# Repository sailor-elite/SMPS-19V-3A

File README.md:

# SMPS SPECIFICATIONS
- Input Voltage: 230V AC (rectified to ~325V DC)
- Output Voltage: 19V DC
- Output Current: 3A
- Output Power: Up to 60W (maximum)

# SCHEMATIC DIAGRAM

# PCB 3D VIEW

# CALCULATION

### Transformer Turns Ratio Calculation

To determine the turns ratio of a transformer, use the following formula:

Np / Ns = Vin / (Vout + Vd)

Where:  
- **\(N_p\)**: Number of primary winding turns  
- **\(N_s\)**: Number of secondary winding turns  
- **\(V_in\)**: Input voltage to the transformer (325V DC in this example)  
- **\(V_out\)**: Desired output voltage (19V DC in this case)  
- **\(V_d\)**: Voltage drop across the secondary diode (approximately 0.5V for a Schottky diode)  

#### Example Calculation:

For an output voltage of 19V:

Np / Ns = 325V / (19V + 0.5V)

Np / Ns = 325 / 19.5 ≈ 16.66

Thus, the primary-to-secondary turns ratio is approximately **17:1**.

### Turns Ratio Calculation

The number of primary turns (**Np**) can be calculated using the volt-second balance equation:

Np = (Vin × ton) / (Bmax × Ae)

Where:  
- **Vin**: Input voltage (325V)  
- **ton**: On-time of the switch (calculated based on the duty cycle, typically 50% at maximum load)  
- **Bmax**: Maximum magnetic flux density (e.g., 2000 Gauss or 0.2T for ferrite cores)  
- **Ae**: Effective cross-sectional area of the core  

#### Example Calculation:

For a switching frequency of **130 kHz** (period = 7.7µs) and a 50% duty cycle, the on-time (\(ton\)) is:

ton = 50% of 7.7µs = 3.35µs

Assume the following parameters for an ETD39 core:  
- **Bmax = 0.2T**  
- **Ae = 125mm² (125 × 10⁻⁶ m²)**  

Substitute the values into the formula:

Np = (325V × 3.35µs) / (0.2T × 125 × 10⁻⁶ m²) Np ≈ 43.5 turns

Thus, the primary winding requires approximately **44 turns**.

### Number of Secondary Turns Calculation

Using the turns ratio and the calculated number of primary turns, the number of secondary turns (**Ns**) can be calculated as follows:

Ns = Np / Turns Ratio

Where:  
- **Np**: Number of primary turns (calculated previously as 85 turns)  
- **Turns Ratio**: Primary-to-secondary turns ratio (17:1 in this example)  

#### Example Calculation:

Substitute the values into the formula:

Ns = 44 / 17 Ns ≈ 2.5 turns

So the turns number is **3**.
### Reference Voltage

Using a voltage divider with resistors of **150 kΩ** and **10.2 kΩ** creates the following ratio:

Vout = Vin * (R_lower / (R_upper + R_lower))

Where:  
- **Vin**: Input voltage  
- **R_lower**: Resistor connected to the ground (10.2 kΩ)  
- **R_upper**: Resistor connected to the input voltage (150 kΩ)  

#### Example Calculation:

For an input voltage of **19V**:

Vout = 19V * (10.2 kΩ / (150 kΩ + 10.2 kΩ))

Vout = 19V * (10.2 / 160.2) ≈ 1.21V

This is very close to the reference voltage of the **MAX6101**, which is **1.25V**.

# COMPONENTS
| Component        | Value          | Package                                    | Quantity |
|------------------|----------------|--------------------------------------------|----------|
| C1               | 0.01uF/275VAC  | Capacitor_THT:C_Rect_L10.0mm_W4.0mm_P7.50mm_MKS4 | 1        |
| C2, C3           | 68uF/450V      | Capacitor_THT:CP_Radial_D12.5mm_P7.50mm    | 2        |
| C4               | 470pF/630V     | Capacitor_SMD:C_1206_3216Metric            | 1        |
| C5               | 22uF/50V       | Capacitor_THT:CP_Radial_D4.0mm_P2.00mm     | 1        |
| C6, C9, C10, C15 | 0.1uF/50V      | -- mixed values --                         | 4        |
| C7               | 4.7uF/50V      | Capacitor_SMD:C_1206_3216Metric            | 1        |
| C8               | 10000pF/100V   | Capacitor_SMD:C_1206_3216Metric            | 1        |
| C11              | 16pF/100V      | Capacitor_SMD:C_1206_3216Metric            | 1        |
| C12              | 10uF/50V       | Capacitor_THT:CP_Radial_D12.5mm_P7.50mm    | 1        |
| C13, C14         | 50uF/120V      | Capacitor_THT:CP_Radial_D12.5mm_P7.50mm    | 2        |
| C16              | 2200pF/100V    | Capacitor_THT:C_Disc_D4.3mm_W1.9mm_P5.00mm | 1        |
| D1               | DF06M          | Diode_THT:Diode_Bridge_DIP-4_W7.62mm_P5.08mm | 1        |
| D2               | 1N4148W        | Diode_SMD:D_SOD-123                        | 1        |
| D3               | UF5406         | Diode_THT:D_DO-201AD_P15.24mm_Horizontal   | 1        |
| D4               | ESD5Zxx        | Diode_SMD:D_SOD-523                        | 1        |
| D5, D6           | SS310          | Diode_SMD:D_SMA                            | 2        |
| F1               | 1000mA         | Fuse:Fuse_Littelfuse-NANO2-462             | 1        |
| J1               | 6160.0159      | private:61600159                           | 1        |
| L1               | L_Coupled_1342 | private:WE-SL5_HC                          | 1        |
| Q1               | BSP135H6433XTMA1| private:SOT230P700X180-4N                  | 1        |
| Q2               | C3M0065090D    | Package_TO_SOT_THT:TO-247-3_Vertical       | 1        |
| R1, R2           | 499K           | Resistor_SMD:R_1206_3216Metric             | 2        |
| R3, R4           | 20K            | Resistor_SMD:R_0805_2012Metric             | 2        |
| R5               | 100            | Resistor_SMD:R_0805_2012Metric             | 1        |
| R6               | 2M             | Resistor_SMD:R_0805_2012Metric             | 1        |
| R7               | 10K            | Resistor_SMD:R_0805_2012Metric             | 1        |
| R8               | 499            | Resistor_SMD:R_0805_2012Metric             | 1        |
| R9               | 14.7K          | Resistor_SMD:R_0805_2012Metric             | 1        |
| R10              | 4.42k          | Resistor_SMD:R_0805_2012Metric             | 1        |
| R11              | 4.75           | Resistor_SMD:R_0805_2012Metric             | 1        |
| R12              | 0.15           | Resistor_THT:R_Axial_DIN0922_L20.0mm_D9.0mm_P25.40mm_Horizontal | 1 |
| R13              | 150k           | Resistor_SMD:R_0805_2012Metric             | 1        |
| R14              | 10.2k          | Resistor_SMD:R_0805_2012Metric             | 1        |
| R15              | 10k            | Resistor_SMD:R_0805_2012Metric             | 1        |
| RV1              | 10D561K        | Varistor:RV_Disc_D7mm_W3.6mm_P5mm          | 1        |
| U1               | LM5023         | Package_SO:VSSOP-8_3.0x3.0mm_P0.65mm       | 1        |
| U2               | PC817          | Package_DIP:DIP-4_W7.62mm                  | 1        |
| U3               | 750313417      | private:SMD_13417_WRE                      | 1        |
| U5               | MAX6101        | Package_TO_SOT_SMD:SOT-23                  | 1        |

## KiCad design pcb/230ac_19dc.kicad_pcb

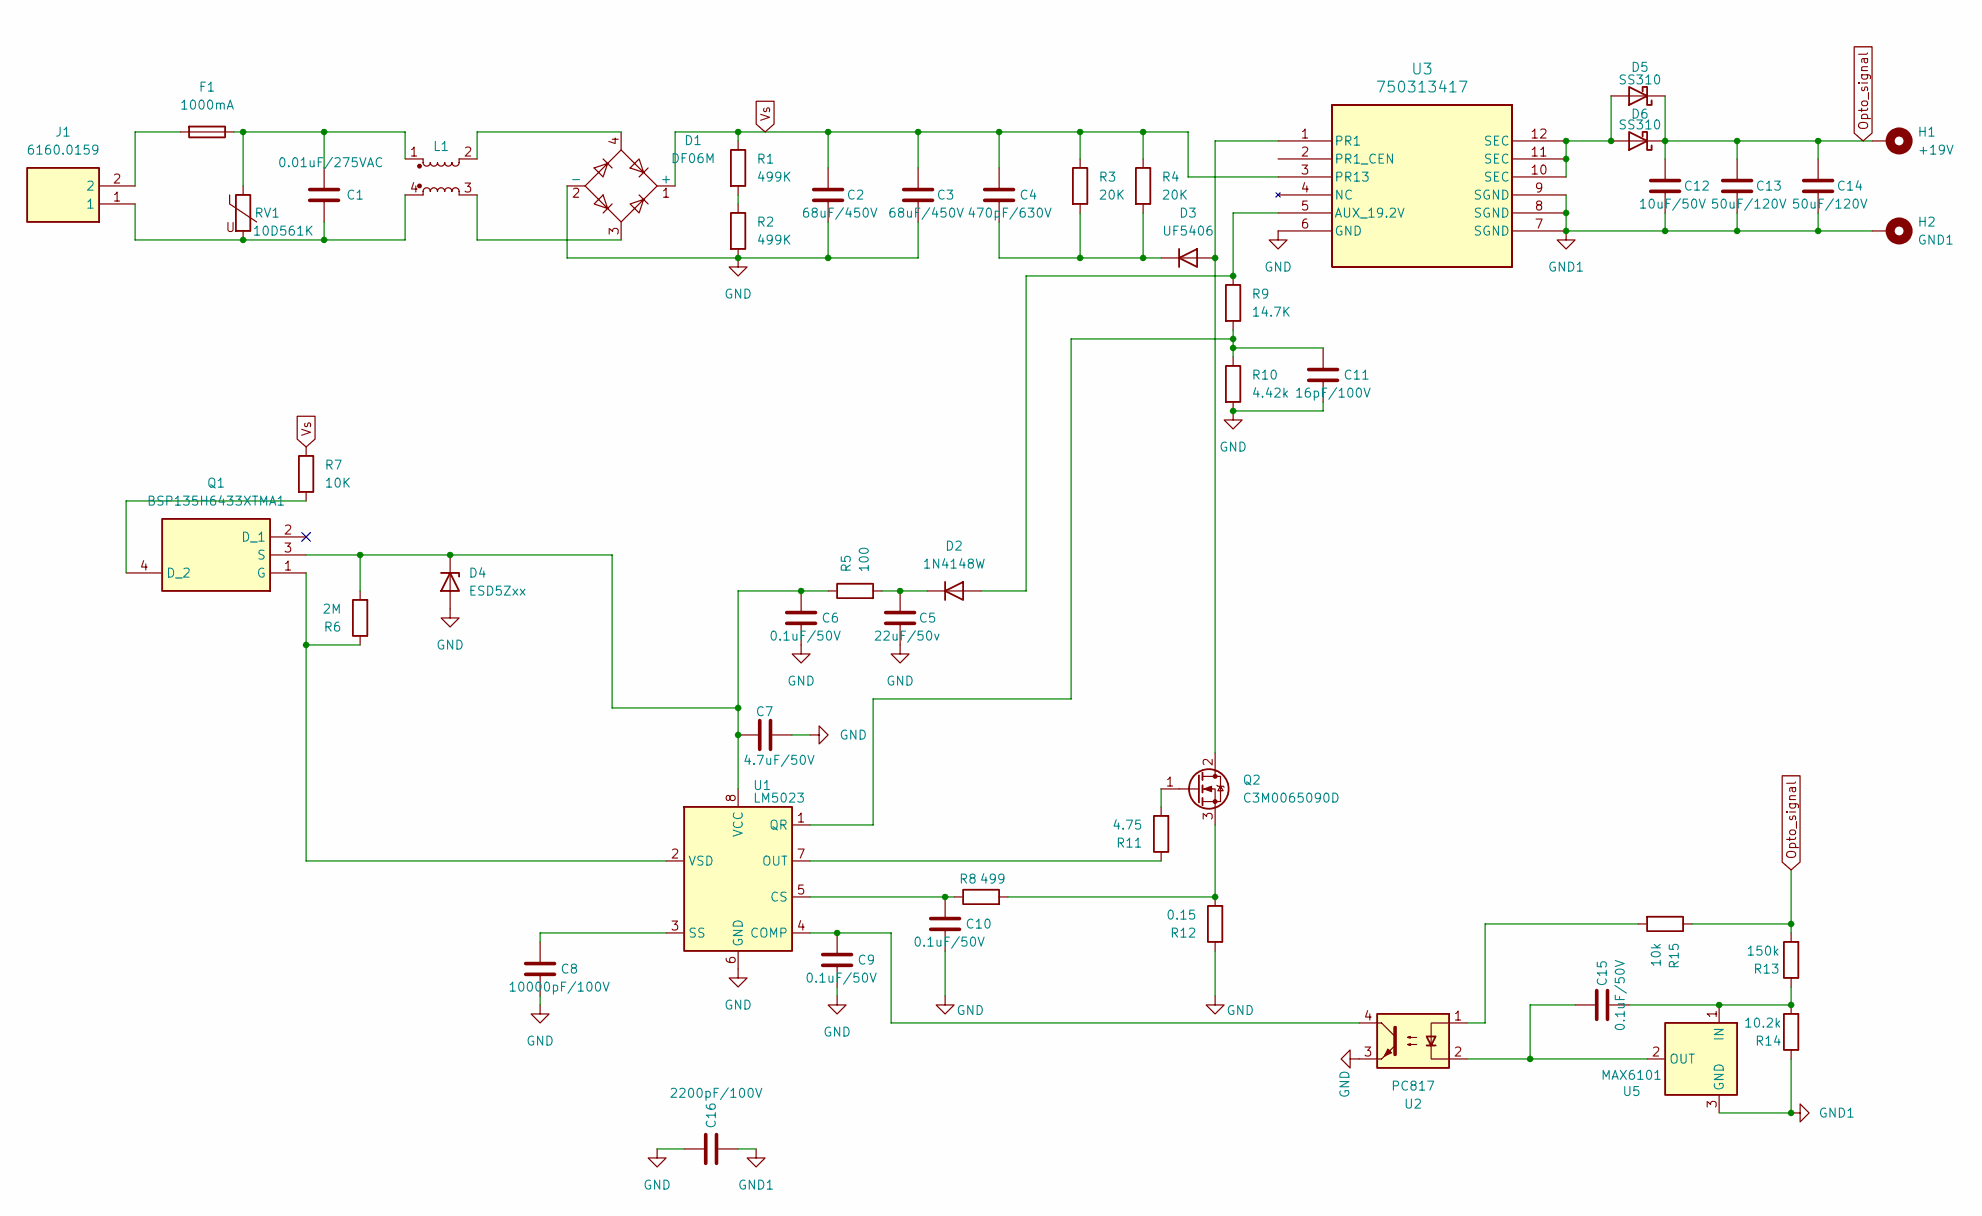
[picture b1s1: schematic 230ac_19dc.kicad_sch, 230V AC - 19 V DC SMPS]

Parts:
C1: 0.01uF/275VAC; C_Rect_L10.0mm_W4.0mm_P7.50mm_MKS4
C2, C3: 68uF/450V; CP_Radial_D12.5mm_P7.50mm
C4: 470pF/630V; C_1206_3216Metric
C5: 22uF/50v; CP_Radial_D4.0mm_P2.00mm
C6, C15: 0.1uF/50V; CP_Radial_D4.0mm_P2.00mm
C7: 4.7uF/50V; C_1206_3216Metric
C8: 10000pF/100V; C_1206_3216Metric
C9, C10: 0.1uF/50V; C_1206_3216Metric
C11: 16pF/100V; C_1206_3216Metric
C12: 10uF/50V; CP_Radial_D12.5mm_P7.50mm
C13, C14: 50uF/120V; CP_Radial_D12.5mm_P7.50mm
C16: 2200pF/100V; C_Disc_D4.3mm_W1.9mm_P5.00mm
D1: DF06M; Diode_Bridge_DIP-4_W7.62mm_P5.08mm
D2: 1N4148W; D_SOD-123
D3: UF5406; D_DO-201AD_P15.24mm_Horizontal
D4: ESD5Zxx; D_SOD-523
D5, D6: SS310; D_SMA
F1: 1000mA; Fuse_Littelfuse-NANO2-462
H1: +19V; TestPoint_THTPad_D2.5mm_Drill1.2mm
H2: GND1; TestPoint_THTPad_D2.5mm_Drill1.2mm
J1: 6160.0159; 61600159; Mouser Part Number 693-6160.0159
L1: L_Coupled_1342; WE-SL5_HC
Q1: BSP135H6433XTMA1; SOT230P700X180-4N; Mouser Part Number 726-BSP135H6433XTMA1
Q2: C3M0065090D; TO-247-3_Vertical
R1, R2: 499K; R_1206_3216Metric
R3, R4: 20K; R_0805_2012Metric
R5: 100; R_0805_2012Metric
R6: 2M; R_0805_2012Metric
R7: 10K; R_0805_2012Metric
R8: 499; R_0805_2012Metric
R9: 14.7K; R_0805_2012Metric
R10: 4.42k; R_0805_2012Metric
R11: 4.75; R_0805_2012Metric
R12: 0.15; R_Axial_DIN0922_L20.0mm_D9.0mm_P25.40mm_Horizontal
R13: 150k; R_0805_2012Metric
R14: 10.2k; R_0805_2012Metric
R15: 10k; R_0805_2012Metric
RV1: 10D561K; RV_Disc_D7mm_W3.6mm_P5mm
U1: LM5023; VSSOP-8_3.0x3.0mm_P0.65mm
U2: PC817; DIP-4_W7.62mm
U3: 750313417; SMD_13417_WRE
U5: MAX6101; SOT-23

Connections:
GND: C2.2, C3.2, C5.2, C6.2, C7.2, C8.2, C9.2, C10.2, C11.2, C16.1, D1.2 (-), D4.2 (A), R2.2, R10.2, R12.1, U1.6 (GND), U2.3, U3.6 (GND)
GND1: C12.2, C13.2, C14.2, C16.2, H2.1, R14.1, U3.7 (SGND), U3.8 (SGND), U3.9 (SGND), U5.3 (GND)
unnamed: C1.1, F1.1, L1.1, RV1.1
unnamed: C1.2, J1.1, L1.4, RV1.2
unnamed: D1.3, L1.3
unnamed: D1.4, L1.2
unnamed: D2.2 (A), R9.1, U3.5 (AUX_19.2V)
unnamed: C5.1, D2.1 (K), R5.2
unnamed: D3.2 (A), Q2.2 (D), U3.1 (PR1)
unnamed: C4.2, D3.1 (K), R3.2, R4.2
unnamed: C6.1, C7.1, D4.1 (K), Q1.3 (S), R5.1, R6.2, U1.8 (VCC)
unnamed: D5.2 (A), D6.2 (A), U3.10 (SEC), U3.11 (SEC), U3.12 (SEC)
unnamed: F1.2, J1.2
unnamed: Q1.4 (D_2), R7.2
unnamed: Q1.1 (G), R6.1, U1.2 (VSD)
unnamed: Q2.1 (G), R11.2
unnamed: Q2.3 (S), R8.2, R12.2
unnamed: R1.2, R2.1
unnamed: R15.2, U2.1
unnamed: C9.1, U1.4 (COMP), U2.4
unnamed: C10.1, R8.1, U1.5 (CS)
unnamed: R11.1, U1.7 (OUT)
unnamed: C11.1, R9.2, R10.1, U1.1 (QR)
unnamed: C8.1, U1.3 (SS)
unnamed: C15.2, R13.1, R14.2, U5.1 (IN)
unnamed: C15.1, U2.2, U5.2 (OUT)
Opto_signal: C12.1, C13.1, C14.1, D5.1 (K), D6.1 (K), H1.1, R13.2, R15.1
Vs: C2.1, C3.1, C4.1, D1.1 (+), R1.1, R3.1, R4.1, R7.1, U3.3 (PR13)

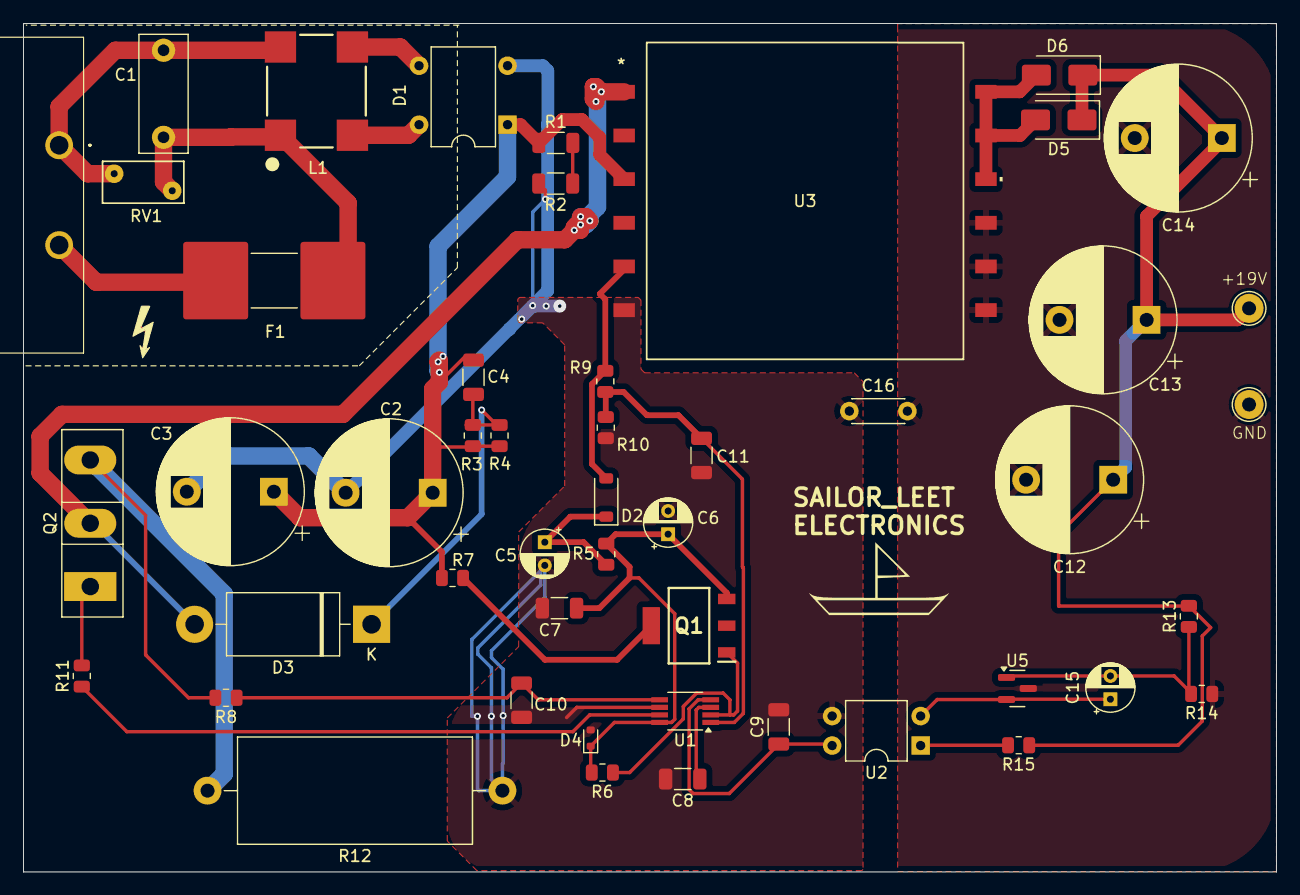
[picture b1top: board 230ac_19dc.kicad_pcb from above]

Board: 2 copper layers, 107.9 x 73.1 mm, 49 parts (0 on the bottom side), 28 nets.

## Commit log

2024-11-27 Rev v1.0
    Only SMPS schematic ( without PCB design)
2024-11-27 Update README.md
    Reworked calculations
2024-12-02 Rev 1.1
    Created PCB design, minor changes to schematic diagram
2024-12-02 Update README.md
    added 3d View and changed components list
2024-12-03 Rev 1.2
    Minor changes in schematic - capacitor symbols
